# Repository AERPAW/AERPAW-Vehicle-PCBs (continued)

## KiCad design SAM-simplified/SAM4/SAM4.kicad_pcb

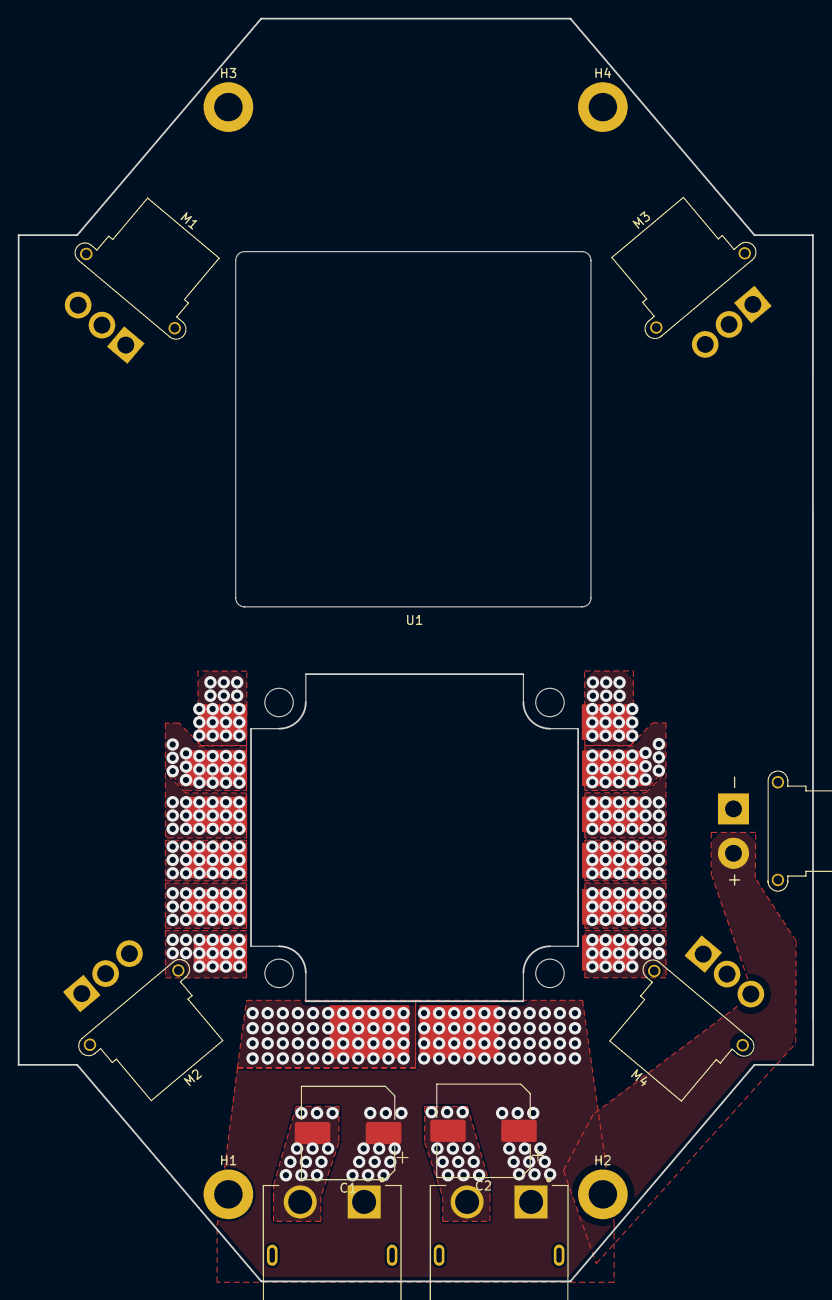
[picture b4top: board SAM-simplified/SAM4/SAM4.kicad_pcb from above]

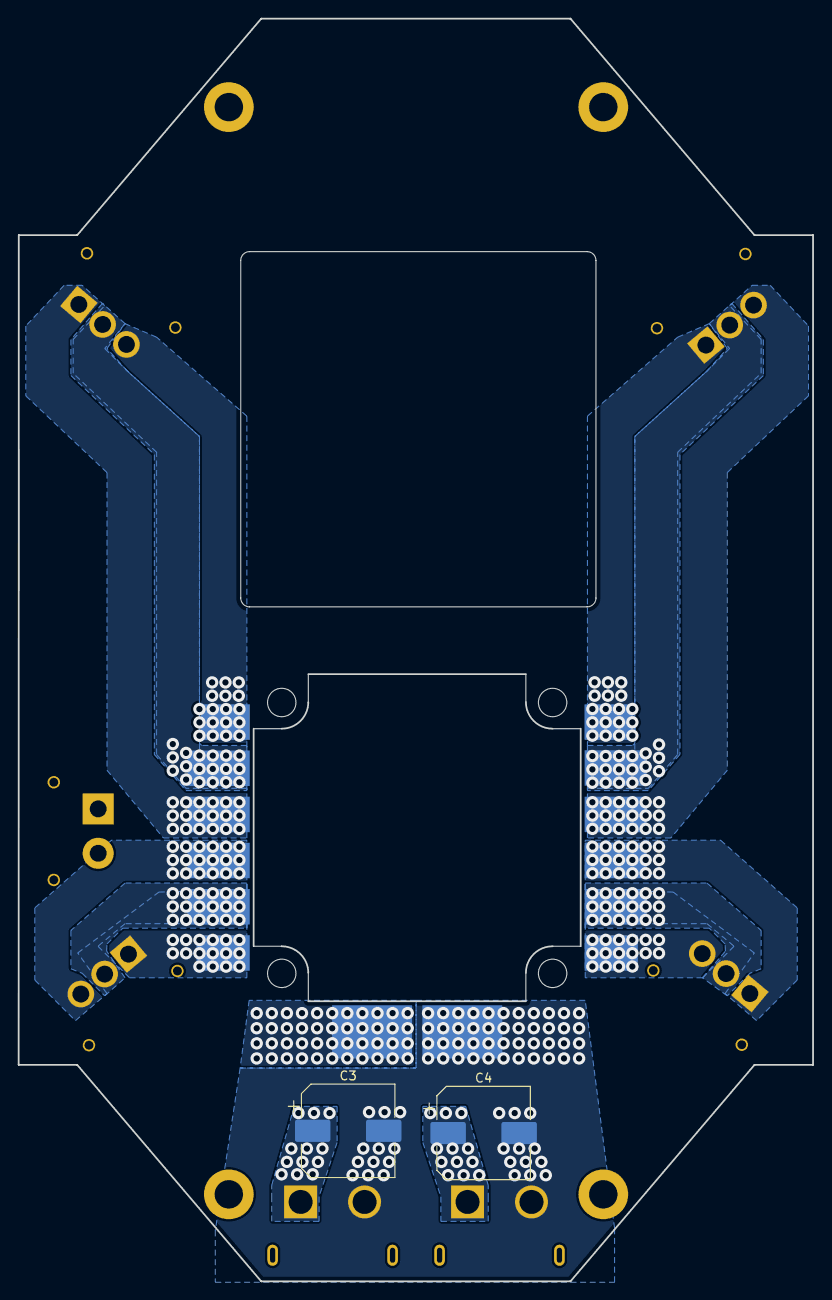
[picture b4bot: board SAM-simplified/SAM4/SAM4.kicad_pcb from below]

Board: 4 copper layers, 89.5 x 142.2 mm, 16 parts (2 on the bottom side), 14 nets, no tracks yet.

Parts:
C1, C2, C3, C4: 330UF 20% 35V SMD; CP_Elec_10x10
H1, H2, H3, H4: MountingHole; MountingHole_3.2mm_M3_DIN965_Pad
J6, J7: XT60PW-M; AMASS_XT60PW-M
J8: XT30PW-F; AMASS_XT30PW-F_1x02_P2.50mm_Horizontal
M1, M2, M3, M4: MR30PW-FB; AMASS_MR30PW-FB_1x03_P3.50mm_Horizontal
U1: T-motor_F55A_PROII; T-motor_55A_ESC

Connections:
+BATT: C1.1, C2.1, C3.1, C4.1, J6.1, J7.1, J8.2, U1.1 (Batt+)
/esc_landing/M1a: M4.1, U1.13 (M1a)
/esc_landing/M1b: M4.2, U1.14 (M1b)
/esc_landing/M1c: M4.3, U1.15 (M1c)
/esc_landing/M2a: M3.1, U1.16 (M2a)
/esc_landing/M2b: M3.2, U1.17 (M2b)
/esc_landing/M2c: M3.3, U1.18 (M2c)
/esc_landing/M3a: M2.3, U1.19 (M3a)
/esc_landing/M3b: M2.2, U1.20 (M3b)
/esc_landing/M3c: M2.1, U1.21 (M3c)
/esc_landing/M4a: M1.3, U1.22 (M4a)
/esc_landing/M4b: M1.2, U1.23 (M4b)
/esc_landing/M4c: M1.1, U1.24 (M4c)
GND: C1.2, C2.2, C3.2, C4.2, J6.2, J7.2, J8.1, U1.2 (Batt-)

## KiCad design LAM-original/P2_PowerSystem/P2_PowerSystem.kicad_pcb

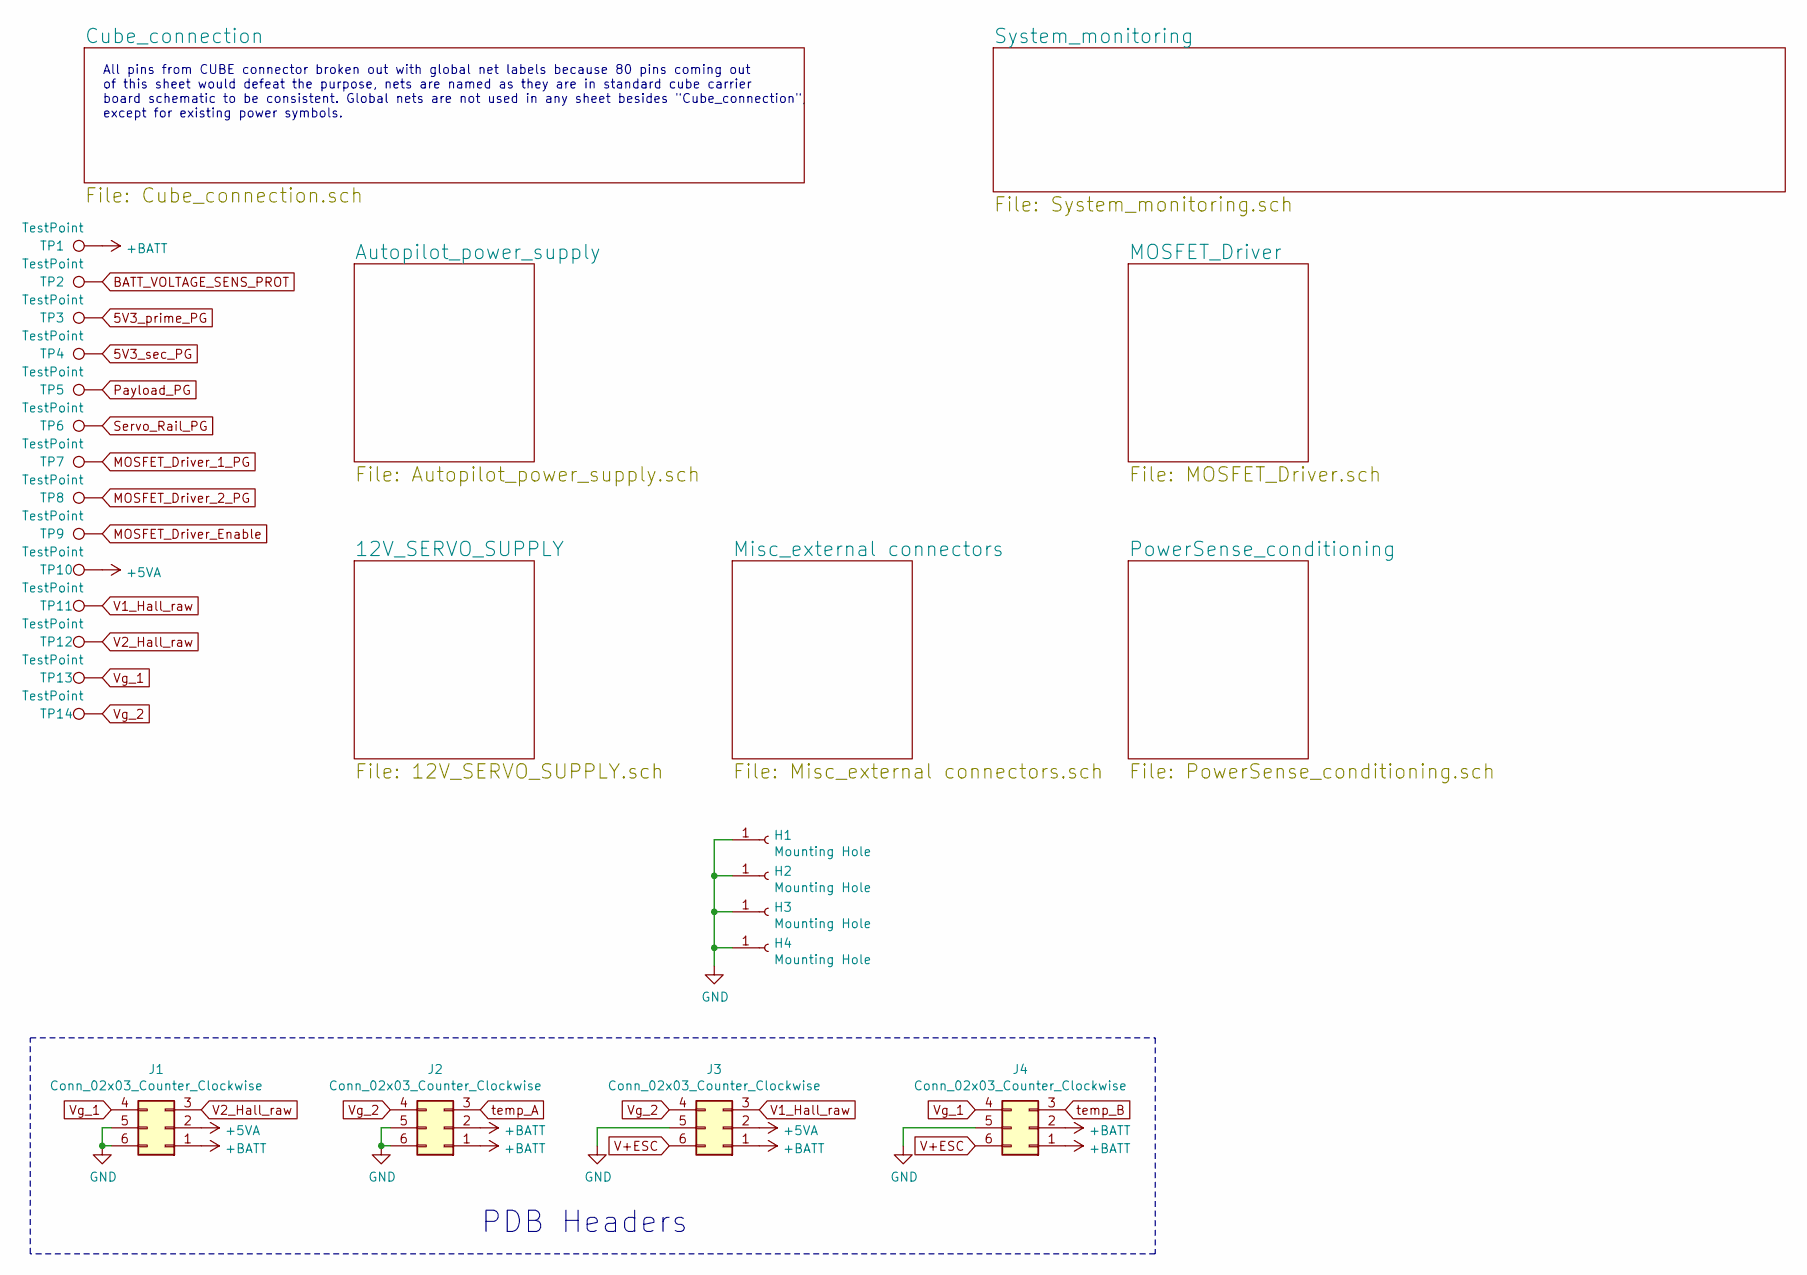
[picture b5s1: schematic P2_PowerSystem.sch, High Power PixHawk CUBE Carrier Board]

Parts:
H1, H2, H3, H4: Mounting Hole; MountingHole_3.2mm_M3_DIN965_Pad; Meta_Part DNP
J1, J2, J3, J4: Conn_02x03_Counter_Clockwise; SAMTEC_ESQ-103-44-L-D; Meta_Part HEADER-F 0.1\" 2x3 POS 19mm THT
TP1, TP2, TP3, TP4, TP5, TP6, TP7, TP8, TP9, TP10, TP11, TP12, TP13, TP14: TestPoint; TestPoint_Pad_1.5x1.5mm; Meta_Part DNP

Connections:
5V3_prime_PG: TP3.1; also elsewhere on the board
5V3_sec_PG: TP4.1; also elsewhere on the board
+5VA: J1.2, J3.2, TP10.1; also elsewhere on the board
+BATT: J1.1, J2.1, J2.2, J3.1, J4.1, J4.2, TP1.1; also elsewhere on the board
BATT_VOLTAGE_SENS_PROT: TP2.1; also elsewhere on the board
GND: H1.1, H2.1, H3.1, H4.1, J1.5, J1.6, J2.5, J2.6, J3.5, J4.5; also elsewhere on the board
MOSFET_Driver_1_PG: TP7.1; also elsewhere on the board
MOSFET_Driver_2_PG: TP8.1; also elsewhere on the board
MOSFET_Driver_Enable: TP9.1; also elsewhere on the board
Payload_PG: TP5.1; also elsewhere on the board
Servo_Rail_PG: TP6.1; also elsewhere on the board
V1_Hall_raw: J3.3, TP11.1; also elsewhere on the board
V2_Hall_raw: J1.3, TP12.1; also elsewhere on the board
V+ESC: J3.6, J4.6; also elsewhere on the board
Vg_1: J1.4, J4.4, TP13.1; also elsewhere on the board
Vg_2: J2.4, J3.4, TP14.1; also elsewhere on the board
temp_A: J2.3; also elsewhere on the board
temp_B: J4.3; also elsewhere on the board

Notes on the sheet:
PDB Headers
All pins from CUBE connector broken out with global net labels because 80 pins coming out of this sheet would defeat the purpose, nets are named as they are in standard cube carrier board schematic to be consistent. Global nets are not used in any sheet besides "Cube_connection", except for existin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

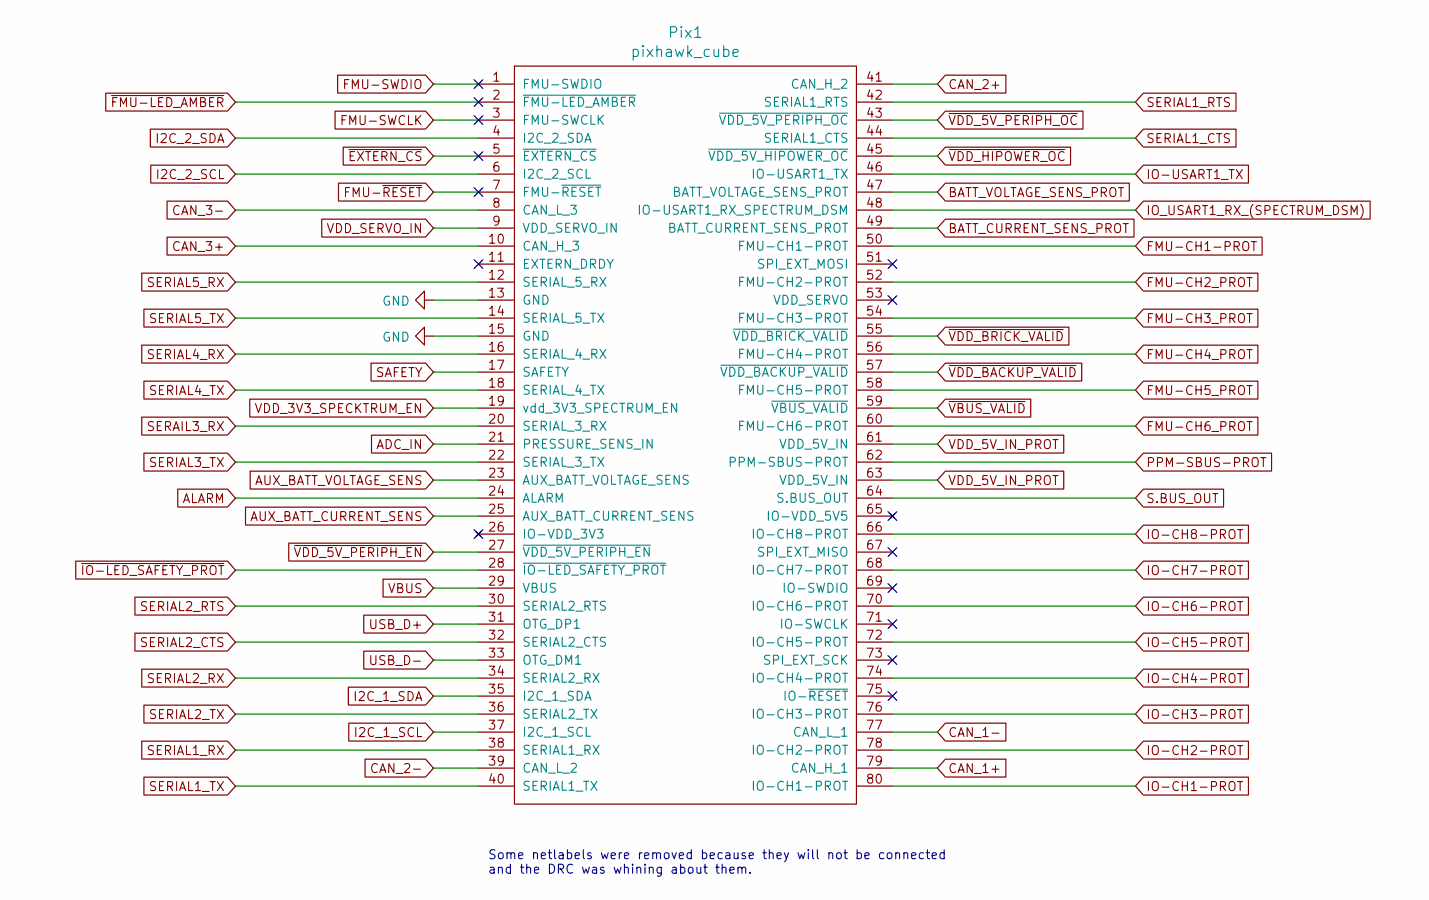
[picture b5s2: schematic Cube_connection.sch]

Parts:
Pix1: pixhawk_cube; DF1710H80DP05V57; Meta_Part DF17 4mm 80POS

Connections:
ADC_IN: Pix1.21 (PRESSURE_SENS_IN); also elsewhere on the board
ALARM: Pix1.24 (ALARM); also elsewhere on the board
AUX_BATT_CURRENT_SENS: Pix1.25 (AUX_BATT_CURRENT_SENS); also elsewhere on the board
AUX_BATT_VOLTAGE_SENS: Pix1.23 (AUX_BATT_VOLTAGE_SENS); also elsewhere on the board
BATT_CURRENT_SENS_PROT: Pix1.49 (BATT_CURRENT_SENS_PROT); also elsewhere on the board
BATT_VOLTAGE_SENS_PROT: Pix1.47 (BATT_VOLTAGE_SENS_PROT); also elsewhere on the board
CAN_1+: Pix1.79 (CAN_H_1); also elsewhere on the board
CAN_1-: Pix1.77 (CAN_L_1); also elsewhere on the board
CAN_2+: Pix1.41 (CAN_H_2); also elsewhere on the board
CAN_2-: Pix1.39 (CAN_L_2); also elsewhere on the board
CAN_3+: Pix1.10 (CAN_H_3); also elsewhere on the board
CAN_3-: Pix1.8 (CAN_L_3); also elsewhere on the board
FMU-CH1-PROT: Pix1.50 (FMU-CH1-PROT); also elsewhere on the board
FMU-CH2_PROT: Pix1.52 (FMU-CH2-PROT); also elsewhere on the board
FMU-CH3_PROT: Pix1.54 (FMU-CH3-PROT); also elsewhere on the board
FMU-CH4_PROT: Pix1.56 (FMU-CH4-PROT); also elsewhere on the board
FMU-CH5_PROT: Pix1.58 (FMU-CH5-PROT); also elsewhere on the board
FMU-CH6_PROT: Pix1.60 (FMU-CH6-PROT); also elsewhere on the board
FMU-SWCLK: Pix1.3 (FMU-SWCLK)
FMU-SWDIO: Pix1.1 (FMU-SWDIO)
FMU-~RESET: Pix1.7 (FMU-~RESET)
GND: Pix1.13 (GND), Pix1.15 (GND); also elsewhere on the board
I2C_1_SCL: Pix1.37 (I2C_1_SCL); also elsewhere on the board
I2C_1_SDA: Pix1.35 (I2C_1_SDA); also elsewhere on the board
I2C_2_SCL: Pix1.6 (I2C_2_SCL); also elsewhere on the board
I2C_2_SDA: Pix1.4 (I2C_2_SDA); also elsewhere on the board
IO-CH1-PROT: Pix1.80 (IO-CH1-PROT); also elsewhere on the board
IO-CH2-PROT: Pix1.78 (IO-CH2-PROT); also elsewhere on the board
IO-CH3-PROT: Pix1.76 (IO-CH3-PROT); also elsewhere on the board
IO-CH4-PROT: Pix1.74 (IO-CH4-PROT); also elsewhere on the board
IO-CH5-PROT: Pix1.72 (IO-CH5-PROT); also elsewhere on the board
IO-CH6-PROT: Pix1.70 (IO-CH6-PROT); also elsewhere on the board
IO-CH7-PROT: Pix1.68 (IO-CH7-PROT); also elsewhere on the board
IO-CH8-PROT: Pix1.66 (IO-CH8-PROT); also elsewhere on the board
IO-USART1_TX: Pix1.46 (IO-USART1_TX)
IO_USART1_RX_(SPECTRUM_DSM): Pix1.48 (IO-USART1_RX_SPECTRUM_DSM)
PPM-SBUS-PROT: Pix1.62 (PPM-SBUS-PROT); also elsewhere on the board
S.BUS_OUT: Pix1.64 (S.BUS_OUT); also elsewhere on the board
SAFETY: Pix1.17 (SAFETY); also elsewhere on the board
SERAIL3_RX: Pix1.20 (SERIAL_3_RX); also elsewhere on the board
SERIAL1_CTS: Pix1.44 (SERIAL1_CTS); also elsewhere on the board
SERIAL1_RTS: Pix1.42 (SERIAL1_RTS); also elsewhere on the board
SERIAL1_RX: Pix1.38 (SERIAL1_RX); also elsewhere on the board
SERIAL1_TX: Pix1.40 (SERIAL1_TX); also elsewhere on the board
SERIAL2_CTS: Pix1.32 (SERIAL2_CTS); also elsewhere on the board
SERIAL2_RTS: Pix1.30 (SERIAL2_RTS); also elsewhere on the board
SERIAL2_RX: Pix1.34 (SERIAL2_RX); also elsewhere on the board
SERIAL2_TX: Pix1.36 (SERIAL2_TX); also elsewhere on the board
SERIAL3_TX: Pix1.22 (SERIAL_3_TX); also elsewhere on the board
SERIAL4_RX: Pix1.16 (SERIAL_4_RX); also elsewhere on the board
SERIAL4_TX: Pix1.18 (SERIAL_4_TX); also elsewhere on the board
SERIAL5_RX: Pix1.12 (SERIAL_5_RX); also elsewhere on the board
SERIAL5_TX: Pix1.14 (SERIAL_5_TX); also elsewhere on the board
USB_D+: Pix1.31 (OTG_DP1); also elsewhere on the board
USB_D-: Pix1.33 (OTG_DM1); also elsewhere on the board
VBUS: Pix1.29 (VBUS); also elsewhere on the board
VDD_3V3_SPECKTRUM_EN: Pix1.19 (vdd_3V3_SPECTRUM_EN); also elsewhere on the board
VDD_5V_IN_PROT: Pix1.61 (VDD_5V_IN), Pix1.63 (VDD_5V_IN); also elsewhere on the board
VDD_SERVO_IN: Pix1.9 (VDD_SERVO_IN); also elsewhere on the board
~EXTERN_CS: Pix1.5 (~EXTERN_CS)
~FMU-LED_AMBER: Pix1.2 (~FMU-LED_AMBER)
~IO-LED_SAFETY_PROT: Pix1.28 (~IO-LED_SAFETY_PROT); also elsewhere on the board
~VBUS_VALID: Pix1.59 (~VBUS_VALID); also elsewhere on the board
~VDD_5V_PERIPH_EN: Pix1.27 (~VDD_5V_PERIPH_EN); also elsewhere on the board
~VDD_5V_PERIPH_OC: Pix1.43 (~VDD_5V_PERIPH_OC); also elsewhere on the board
~VDD_BACKUP_VALID: Pix1.57 (~VDD_BACKUP_VALID); also elsewhere on the board
~VDD_BRICK_VALID: Pix1.55 (~VDD_BRICK_VALID); also elsewhere on the board
~VDD_HIPOWER_OC: Pix1.45 (~VDD_5V_HIPOWER_OC); also elsewhere on the board

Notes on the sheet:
Some netlabels were removed because they will not be connected and the DRC was whining about them.

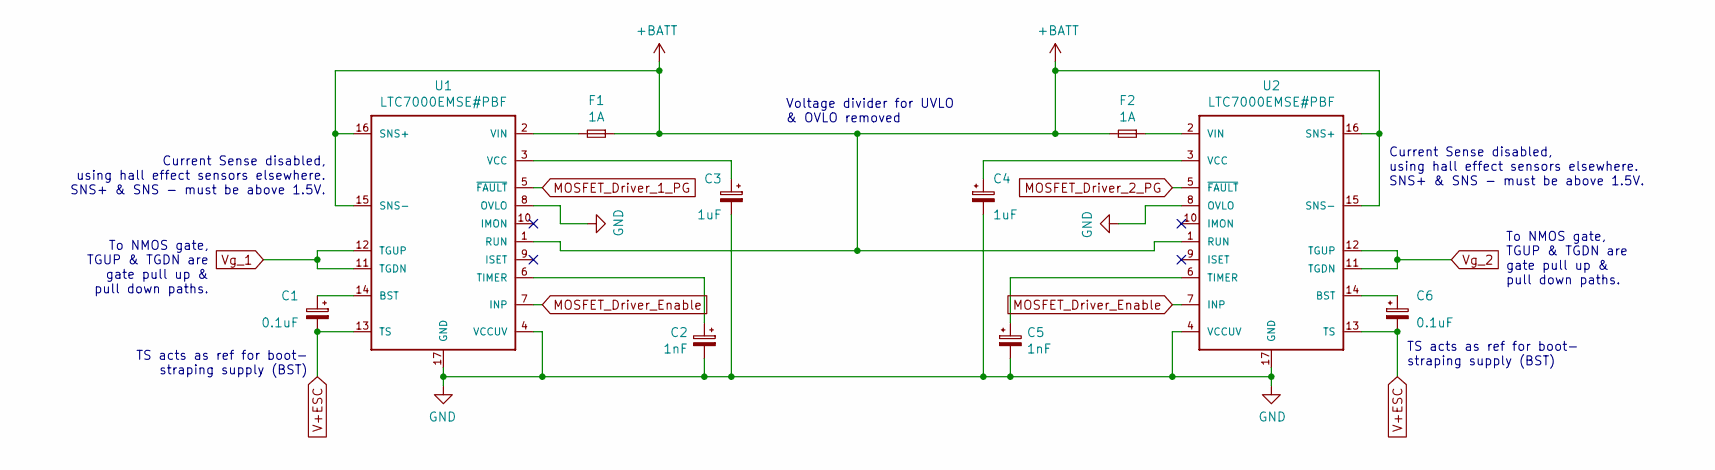
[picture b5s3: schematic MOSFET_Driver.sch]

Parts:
C1, C6: 0.1uF; C_1206_3216Metric; Meta_Part CAP CER 0.1UF 50V 1206
C2, C5: 1nF; C_1206_3216Metric; Meta_Part CAP CER 1NF 50V 1206
C3, C4: 1uF; C_1206_3216Metric; Meta_Part CAP CER 1UF 50V 1206
F1, F2: 1A; Fuse_1206_3216Metric_Pad1.42x1.75mm_HandSolder; Meta_Part FUSE SMD 1A 60VDC 1206
U1, U2: LTC7000EMSE#PBF; SOP50P490X110-17N; Meta_Part LTC7000EMSE#PBF

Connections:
+BATT: F1.1, F2.2, U1.1 (RUN), U1.15 (SNS-), U1.16 (SNS+), U2.1 (RUN), U2.15 (SNS-), U2.16 (SNS+); also elsewhere on the board
GND: C2.2, C3.2, C4.2, C5.2, U1.4 (VCCUV), U1.8 (OVLO), U1.17 (GND), U2.4 (VCCUV), U2.8 (OVLO), U2.17 (GND); also elsewhere on the board
MOSFET_Driver_1_PG: U1.5 (~FAULT~); also elsewhere on the board
MOSFET_Driver_2_PG: U2.5 (~FAULT~); also elsewhere on the board
MOSFET_Driver_Enable: U1.7 (INP), U2.7 (INP); also elsewhere on the board
unnamed: C1.1, U1.14 (BST)
unnamed: C2.1, U1.6 (TIMER)
unnamed: C3.1, U1.3 (VCC)
unnamed: C4.1, U2.3 (VCC)
unnamed: C5.1, U2.6 (TIMER)
unnamed: C6.1, U2.14 (BST)
unnamed: F1.2, U1.2 (VIN)
unnamed: F2.1, U2.2 (VIN)
V+ESC: C1.2, C6.2, U1.13 (TS), U2.13 (TS); also elsewhere on the board
Vg_1: U1.11 (TGDN), U1.12 (TGUP); also elsewhere on the board
Vg_2: U2.11 (TGDN), U2.12 (TGUP); also elsewhere on the board

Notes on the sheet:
Current Sense disabled, using hall effect sensors elsewhere. SNS+ & SNS - must be above 1.5V.
TS acts as ref for boot- straping supply (BST)
To NMOS gate, TGUP & TGDN are gate pull up & pull down paths.
Voltage divider for UVLO & OVLO removed

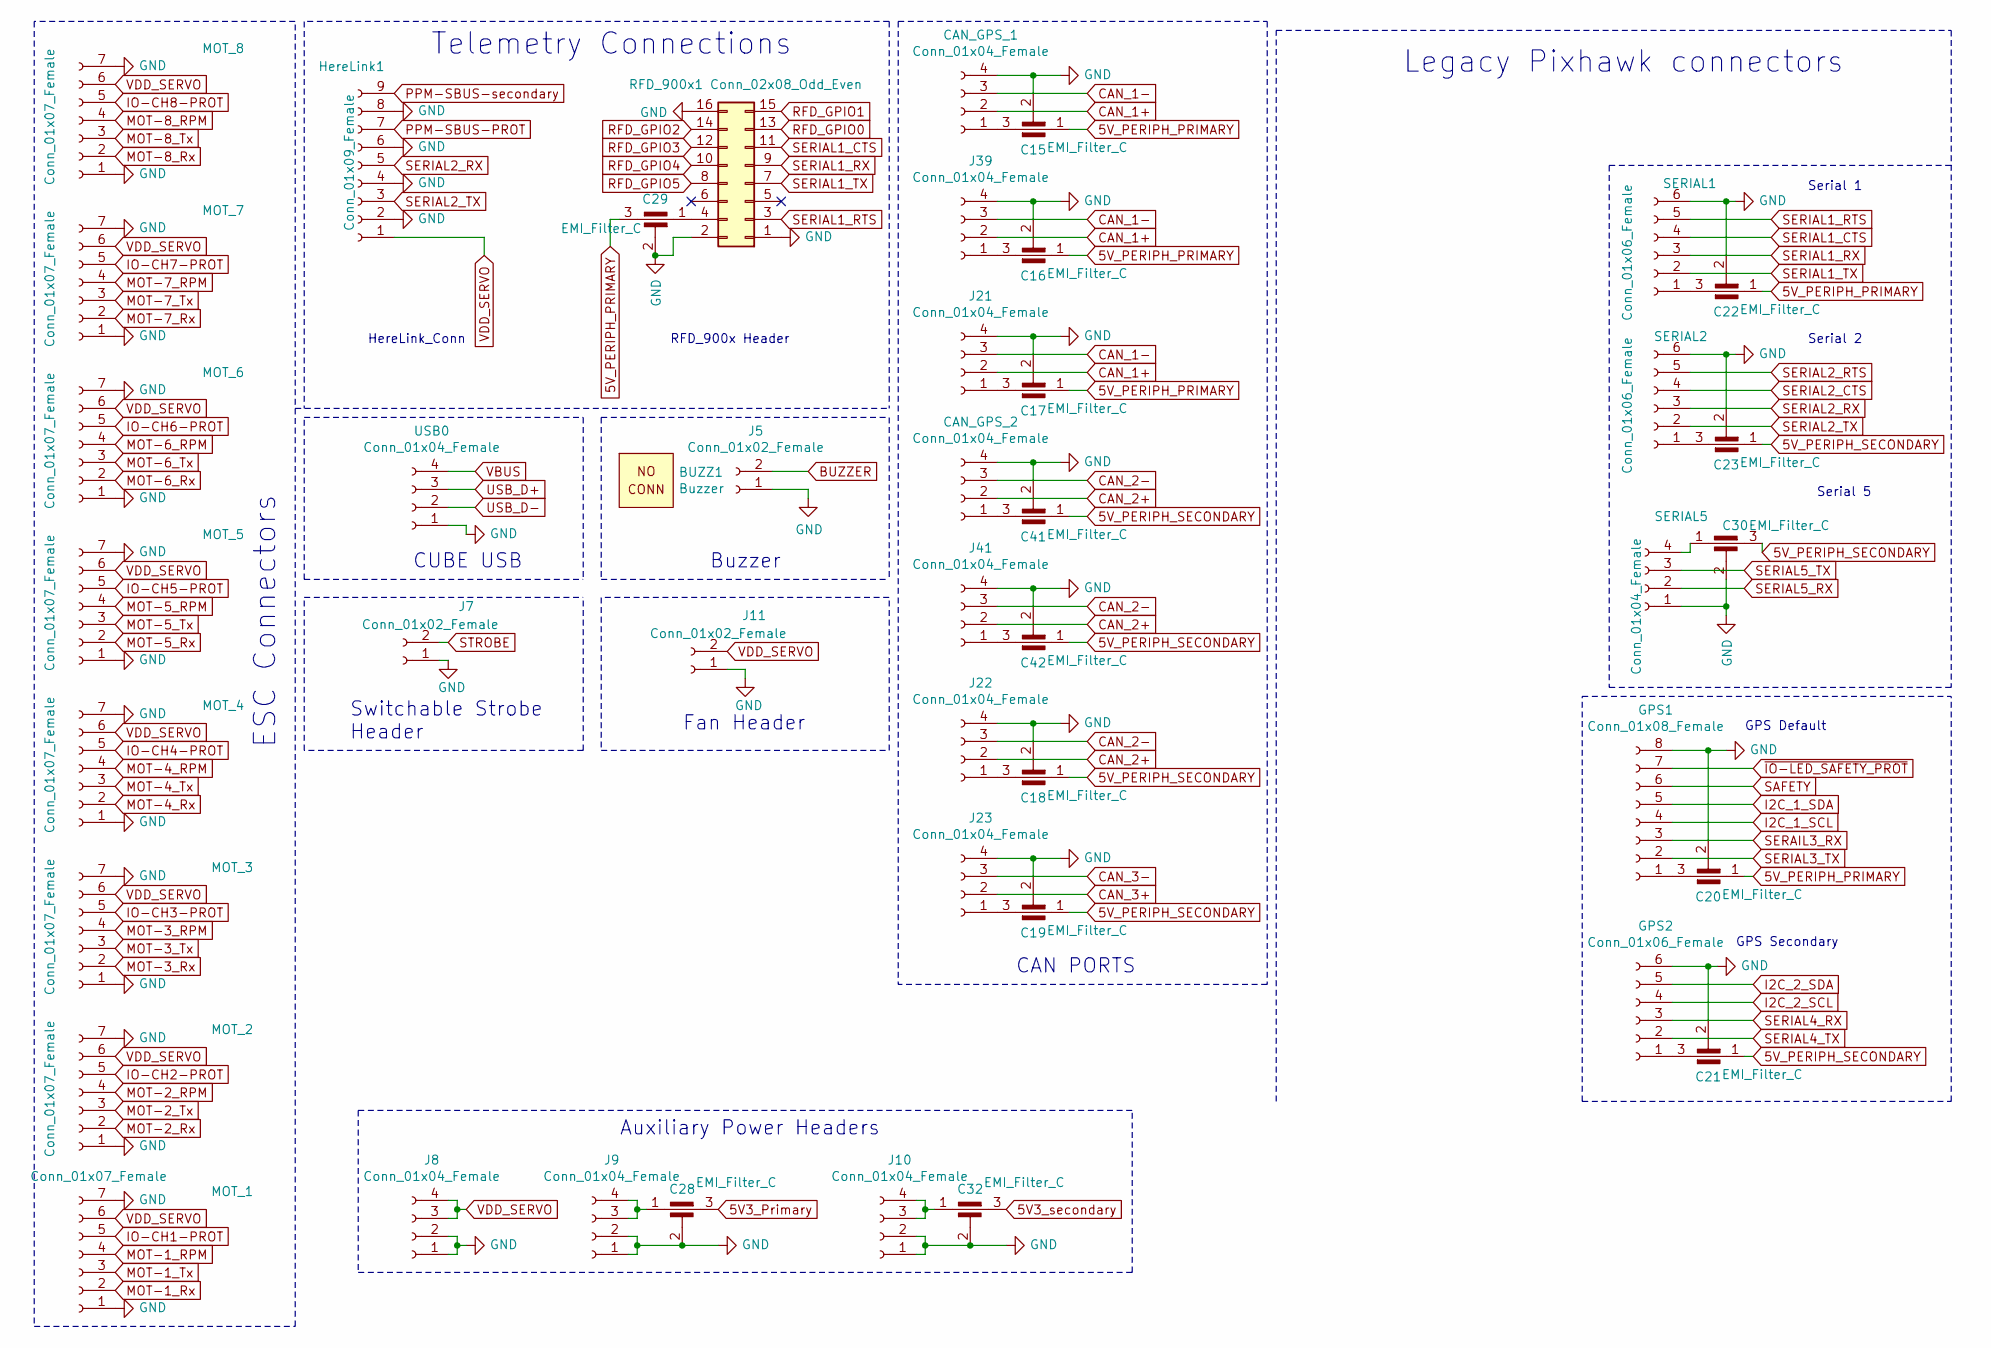
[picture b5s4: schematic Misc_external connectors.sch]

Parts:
BUZZ1: Buzzer; BUZZER; Meta_Part Piezo buzzer
C15, C16, C17, C18, C19, C20, C21, C22, C23, C28, C29, C30, C32, C41, C42: EMI_Filter_C; FIL_NFM21HC224R1A3D; Meta_Part NFM21HC224R1A3D
CAN_GPS_1, CAN_GPS_2: Conn_01x04_Female; JST_GH_SM04B-GHS-TB_1x04-1MP_P1.25mm_Horizontal; Meta_Part JST-GH 4POS HEADER HORZ
GPS1: Conn_01x08_Female; JST_GH_BM08B-GHS-TBT_1x08-1MP_P1.25mm_Vertical; Meta_Part JST-GH 8POS HEADER VERT
GPS2: Conn_01x06_Female; JST_GH_BM06B-GHS-TBT_1x06-1MP_P1.25mm_Vertical; Meta_Part JST-GH 6POS HEADER VERT
HereLink1: Conn_01x09_Female; JST_GH_SM09B-GHS-TB_1x09-1MP_P1.25mm_Horizontal; Meta_Part JST-GH 9POS HEADER HORZ
J5: Conn_01x02_Female; BUZZ_CONN; Meta_Part DNP
J7, J11: Conn_01x02_Female; Molex_CLIK-Mate_502386-0270_1x02-1MP_P1.25mm_Horizontal; Meta_Part CLIK-Mate 1.25mm 2POS HORZ
J8, J9, J10: Conn_01x04_Female; Molex_CLIK-Mate_502382-0470_1x04-1MP_P1.25mm_Vertical; Meta_Part CLIK-Mate 1.25mm 4POS VERT
J21, J23, J39, J41: Conn_01x04_Female; JST_GH_BM04B-GHS-TBT_1x04-1MP_P1.25mm_Vertical; Meta_Part JST-GH 4POS HEADER VERT
J22: Conn_01x04_Female; JST_GH_SM04B-GHS-TB_1x04-1MP_P1.25mm_Horizontal; Meta_Part JST-GH 4POS HEADER HORZ
MOT_1, MOT_2, MOT_3, MOT_4, MOT_5, MOT_6, MOT_7, MOT_8: Conn_01x07_Female; JST_GH_SM07B-GHS-TB_1x07-1MP_P1.25mm_Horizontal; Meta_Part JST-GH 7POS HEADER HORZ
RFD_900x1: Conn_02x08_Odd_Even; RFD900_2x08_2.54mm; Meta_Part HEADER-F 0.1\" 2x8 POS THT
SERIAL1, SERIAL2: Conn_01x06_Female; JST_GH_BM06B-GHS-TBT_1x06-1MP_P1.25mm_Vertical; Meta_Part JST-GH 6POS HEADER VERT
SERIAL5: Conn_01x04_Female; JST_GH_BM04B-GHS-TBT_1x04-1MP_P1.25mm_Vertical; Meta_Part JST-GH 4POS HEADER VERT
USB0: Conn_01x04_Female; JST_GH_BM04B-GHS-TBT_1x04-1MP_P1.25mm_Vertical; Meta_Part JST-GH 4POS HEADER VERT

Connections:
5V3_Primary: C28.3; also elsewhere on the board
5V3_secondary: C32.3; also elsewhere on the board
5V_PERIPH_PRIMARY: C15.1, C16.1, C17.1, C20.1, C22.1, C29.3; also elsewhere on the board
5V_PERIPH_SECONDARY: C18.1, C19.1, C21.1, C23.1, C30.3, C41.1, C42.1; also elsewhere on the board
BUZZER: J5.2; also elsewhere on the board
CAN_1+: CAN_GPS_1.2, J21.2, J39.2; also elsewhere on the board
CAN_1-: CAN_GPS_1.3, J21.3, J39.3; also elsewhere on the board
CAN_2+: CAN_GPS_2.2, J22.2, J41.2; also elsewhere on the board
CAN_2-: CAN_GPS_2.3, J22.3, J41.3; also elsewhere on the board
CAN_3+: J23.2; also elsewhere on the board
CAN_3-: J23.3; also elsewhere on the board
GND: C15.2, C16.2, C17.2, C18.2, C19.2, C20.2, C21.2, C22.2, C23.2, C28.2, C29.2, C30.2, C32.2, C41.2, C42.2, CAN_GPS_1.4, CAN_GPS_2.4, GPS1.8, GPS2.6, HereLink1.2, HereLink1.4, HereLink1.6, HereLink1.8, J5.1, J7.1, J8.1, J8.2, J9.1, J9.2, J10.1, J10.2, J11.1, J21.4, J22.4, J23.4, J39.4, J41.4, MOT_1.1, MOT_1.7, MOT_2.1, MOT_2.7, MOT_3.1, MOT_3.7, MOT_4.1, MOT_4.7, MOT_5.1, MOT_5.7, MOT_6.1, MOT_6.7, MOT_7.1, MOT_7.7, MOT_8.1, MOT_8.7, RFD_900x1.1, RFD_900x1.2, RFD_900x1.16, SERIAL1.6, SERIAL2.6, SERIAL5.1, USB0.1; also elsewhere on the board
I2C_1_SCL: GPS1.4; also elsewhere on the board
I2C_1_SDA: GPS1.5; also elsewhere on the board
I2C_2_SCL: GPS2.4; also elsewhere on the board
I2C_2_SDA: GPS2.5; also elsewhere on the board
IO-CH1-PROT: MOT_1.5; also elsewhere on the board
IO-CH2-PROT: MOT_2.5; also elsewhere on the board
IO-CH3-PROT: MOT_3.5; also elsewhere on the board
IO-CH4-PROT: MOT_4.5; also elsewhere on the board
IO-CH5-PROT: MOT_5.5; also elsewhere on the board
IO-CH6-PROT: MOT_6.5; also elsewhere on the board
IO-CH7-PROT: MOT_7.5; also elsewhere on the board
IO-CH8-PROT: MOT_8.5; also elsewhere on the board
MOT-1_RPM: MOT_1.4; also elsewhere on the board
MOT-1_Rx: MOT_1.2; also elsewhere on the board
MOT-1_Tx: MOT_1.3; also elsewhere on the board
MOT-2_RPM: MOT_2.4; also elsewhere on the board
MOT-2_Rx: MOT_2.2; also elsewhere on the board
MOT-2_Tx: MOT_2.3; also elsewhere on the board
MOT-3_RPM: MOT_3.4; also elsewhere on the board
MOT-3_Rx: MOT_3.2; also elsewhere on the board
MOT-3_Tx: MOT_3.3; also elsewhere on the board
MOT-4_RPM: MOT_4.4; also elsewhere on the board
MOT-4_Rx: MOT_4.2; also elsewhere on the board
MOT-4_Tx: MOT_4.3; also elsewhere on the board
MOT-5_RPM: MOT_5.4; also elsewhere on the board
MOT-5_Rx: MOT_5.2; also elsewhere on the board
MOT-5_Tx: MOT_5.3; also elsewhere on the board
MOT-6_RPM: MOT_6.4; also elsewhere on the board
MOT-6_Rx: MOT_6.2; also elsewhere on the board
MOT-6_Tx: MOT_6.3; also elsewhere on the board
MOT-7_RPM: MOT_7.4; also elsewhere on the board
MOT-7_Rx: MOT_7.2; also elsewhere on the board
MOT-7_Tx: MOT_7.3; also elsewhere on the board
MOT-8_RPM: MOT_8.4; also elsewhere on the board
MOT-8_Rx: MOT_8.2; also elsewhere on the board
MOT-8_Tx: MOT_8.3; also elsewhere on the board
unnamed: C15.3, CAN_GPS_1.1
unnamed: C16.3, J39.1
unnamed: C17.3, J21.1
unnamed: C18.3, J22.1
unnamed: C19.3, J23.1
unnamed: C20.3, GPS1.1
unnamed: C21.3, GPS2.1
unnamed: C22.3, SERIAL1.1
unnamed: C23.3, SERIAL2.1
unnamed: C28.1, J9.3, J9.4
unnamed: C29.1, RFD_900x1.4
unnamed: C30.1, SERIAL5.4
unnamed: C32.1, J10.3, J10.4
unnamed: C41.3, CAN_GPS_2.1
unnamed: C42.3, J41.1
PPM-SBUS-PROT: HereLink1.7; also elsewhere on the board
PPM-SBUS-secondary: HereLink1.9; also elsewhere on the board
RFD_GPIO0: RFD_900x1.13; also elsewhere on the board
RFD_GPIO1: RFD_900x1.15; also elsewhere on the board
RFD_GPIO2: RFD_900x1.14; also elsewhere on the board
RFD_GPIO3: RFD_900x1.12; also elsewhere on the board
RFD_GPIO4: RFD_900x1.10
RFD_GPIO5: RFD_900x1.8
SAFETY: GPS1.6; also elsewhere on the board
SERAIL3_RX: GPS1.3; also elsewhere on the board
SERIAL1_CTS: RFD_900x1.11, SERIAL1.4; also elsewhere on the board
SERIAL1_RTS: RFD_900x1.3, SERIAL1.5; also elsewhere on the board
SERIAL1_RX: RFD_900x1.9, SERIAL1.3; also elsewhere on the board
SERIAL1_TX: RFD_900x1.7, SERIAL1.2; also elsewhere on the board
SERIAL2_CTS: SERIAL2.4; also elsewhere on the board
SERIAL2_RTS: SERIAL2.5; also elsewhere on the board
SERIAL2_RX: HereLink1.5, SERIAL2.3; also elsewhere on the board
SERIAL2_TX: HereLink1.3, SERIAL2.2; also elsewhere on the board
SERIAL3_TX: GPS1.2; also elsewhere on the board
SERIAL4_RX: GPS2.3; also elsewhere on the board
SERIAL4_TX: GPS2.2; also elsewhere on the board
SERIAL5_RX: SERIAL5.2; also elsewhere on the board
SERIAL5_TX: SERIAL5.3; also elsewhere on the board
STROBE: J7.2; also elsewhere on the board
USB_D+: USB0.3; also elsewhere on the board
USB_D-: USB0.2; also elsewhere on the board
VBUS: USB0.4; also elsewhere on the board
VDD_SERVO: HereLink1.1, J8.3, J8.4, J11.2, MOT_1.6, MOT_2.6, MOT_3.6, MOT_4.6, MOT_5.6, MOT_6.6, MOT_7.6, MOT_8.6; also elsewhere on the board
~IO-LED_SAFETY_PROT: GPS1.7; also elsewhere on the board

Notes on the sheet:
ESC Connectors
HereLink_Conn
CAN PORTS
GPS Default
GPS Secondary
RFD_900x Header
Serial 2
Serial 1
Legacy Pixhawk connectors
Telemetry Connections
Fan Header
Switchable Strobe Header
Auxiliary Power Headers
CUBE USB
Buzzer
Serial 5

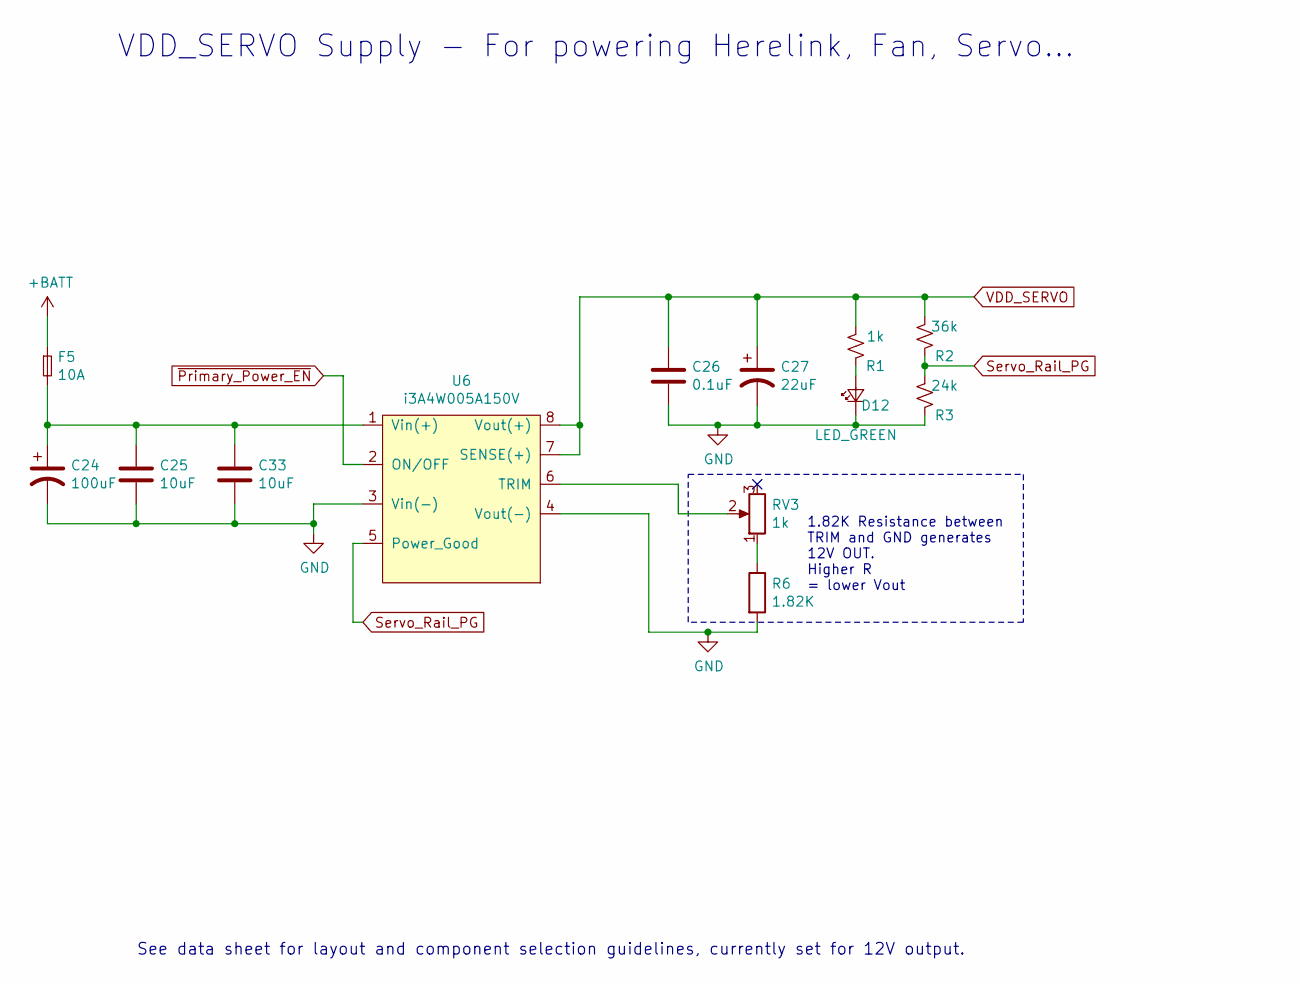
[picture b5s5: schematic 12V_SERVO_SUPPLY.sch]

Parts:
C24: 100uF; CP_Elec_10x10.5; Meta_Part CAP ALUM 100UF 20% 63V SMD
C25, C33: 10uF; C_1206_3216Metric; Meta_Part CAP CER 10UF 50V 1206
C26: 0.1uF; C_1206_3216Metric; Meta_Part CAP CER 0.1UF 50V 1206
C27: 22uF; C_1206_3216Metric; Meta_Part CAP CER 22UF 35V 1206
D12: LED_GREEN; LED_1206_3216Metric; Meta_Part LED SMD GREEN 1206
F5: 10A; Fuse_2512_6332Metric_Pad1.52x3.35mm_HandSolder; Meta_Part FUSE SMD 10A 60VDC 2-SMD
R1: 1k; R_1206_3216Metric; Meta_Part RES 1K OHM 1% 1/4W 1206
R2: 36k; R_1206_3216Metric; Meta_Part RES 36k OHM 1% 1/4W 1206
R3: 24k; R_1206_3216Metric; Meta_Part RES 24k OHM 1% 1/4W 1206
R6: 1.82K; R_1206_3216Metric; Meta_Part RES 1.82k OHM 1% 1/4W 1206
RV3: 1k; Potentiometer_Bourns_3266W_Vertical; Meta_Part 12 TURN TRIMMER 1K OHM 0.25W PC PIN TOP
U6: i3A4W005A150V; 1_32nd_Brick_8pin; Meta_Part i3A4W005A150V

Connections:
+BATT: F5.1; also elsewhere on the board
GND: C24.2, C25.2, C26.2, C27.2, C33.2, D12.1 (K), R3.2, R6.2, U6.3 (Vin(-)), U6.4 (Vout(-)); also elsewhere on the board
unnamed: C24.1, C25.1, C33.1, F5.2, U6.1 (Vin(+))
unnamed: D12.2 (A), R1.2
unnamed: R6.1, RV3.1
unnamed: RV3.2, U6.6 (TRIM)
Servo_Rail_PG: R2.2, R3.1, U6.5 (Power_Good); also elsewhere on the board
VDD_SERVO: C26.1, C27.1, R1.1, R2.1, U6.7 (SENSE(+)), U6.8 (Vout(+)); also elsewhere on the board
~Primary_Power_EN: U6.2 (ON/OFF); also elsewhere on the board

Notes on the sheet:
VDD_SERVO Supply - For powering Herelink, Fan, Servo...
See data sheet for layout and component selection guidelines, currently set for 12V output.
1.82K Resistance between TRIM and GND generates 12V OUT. Higher R = lower Vout
